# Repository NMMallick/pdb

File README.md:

## [Link to TPS56339 Datasheet](https://www.ti.com/lit/gpn/tps56339)

# Layout

# Schematic

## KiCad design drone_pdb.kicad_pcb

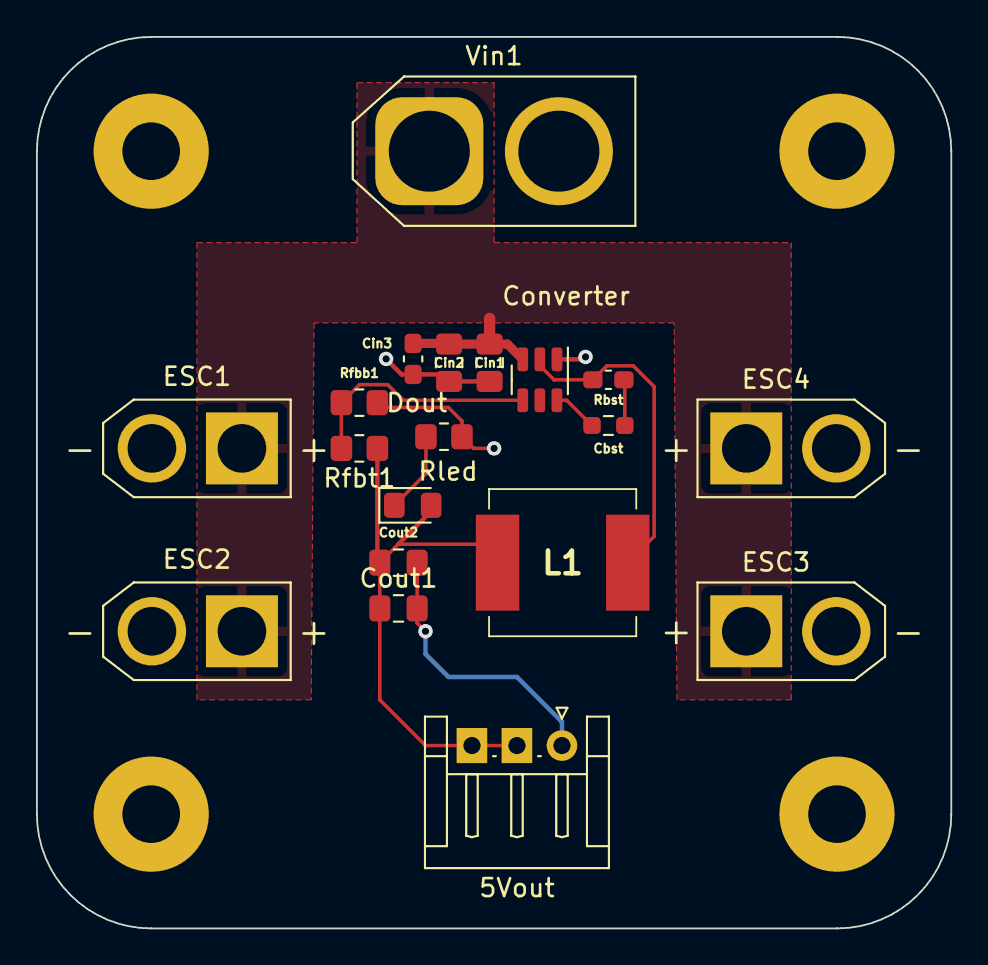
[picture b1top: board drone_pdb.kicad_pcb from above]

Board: 2 copper layers, 50.8 x 49.5 mm, 19 parts (0 on the bottom side), 8 nets.

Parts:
5Vout: Conn_01x03_Male; JST_EH_S3B-EH_1x03_P2.50mm_Horizontal
Cbst: 100nF; C_0603_1608Metric_Pad1.08x0.95mm_HandSolder
Cin1, Cin2: 1uF; C_0805_2012Metric_Pad1.18x1.45mm_HandSolder
Cin3: 100nF; C_0603_1608Metric_Pad1.08x0.95mm_HandSolder
Converter: TPS56339DDC; SOT-23-6
Cout1, Cout2: 22uF; C_0805_2012Metric_Pad1.18x1.45mm_HandSolder
Dout: LED; LED_0805_2012Metric_Pad1.15x1.40mm_HandSolder
ESC1, ESC2, ESC3, ESC4: Conn_01x02_Female; AMASS_XT30U-F_1x02_P5.0mm_Vertical
L1: 5.6uH; IHLP3232DZER330M11
Rbst: 300Ohm; R_0603_1608Metric_Pad0.98x0.95mm_HandSolder
Rfbb1: 10kOhm; R_0805_2012Metric_Pad1.20x1.40mm_HandSolder
Rfbt1: 52.3kOhm; R_0805_2012Metric_Pad1.20x1.40mm_HandSolder
Rled: 5kOhm; R_0805_2012Metric_Pad1.20x1.40mm_HandSolder
Vin1: 24V; AMASS_XT60-M_1x02_P7.20mm_Vertical

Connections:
/Vout: 5Vout.2, 5Vout.3, Cout1.1, Cout2.1, Dout.2 (A), L1.2, Rfbt1.1
GND: 5Vout.1, Cin1.2, Cin2.2, Cin3.2, Converter.1 (GND), Cout1.2, Cout2.2, ESC1.1, ESC2.1, ESC3.1, ESC4.1, Rfbb1.2, Rled.2, Vin1.2 (-)
unnamed: Cbst.1, Rbst.2
unnamed: Cbst.2, Converter.2 (SW), L1.1
unnamed: Converter.4 (FB), Rfbb1.1, Rfbt1.2
unnamed: Converter.6 (BOOT), Rbst.1
unnamed: Dout.1 (K), Rled.1
VCC: Cin1.1, Cin2.1, Cin3.1, Converter.3 (VIN), ESC1.2, ESC2.2, ESC3.2, ESC4.2, Vin1.1 (+)

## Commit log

2024-06-11 init
2024-06-11 added pngs
2024-06-11 Update README.md
    added links
2024-06-11 fixed layout png
